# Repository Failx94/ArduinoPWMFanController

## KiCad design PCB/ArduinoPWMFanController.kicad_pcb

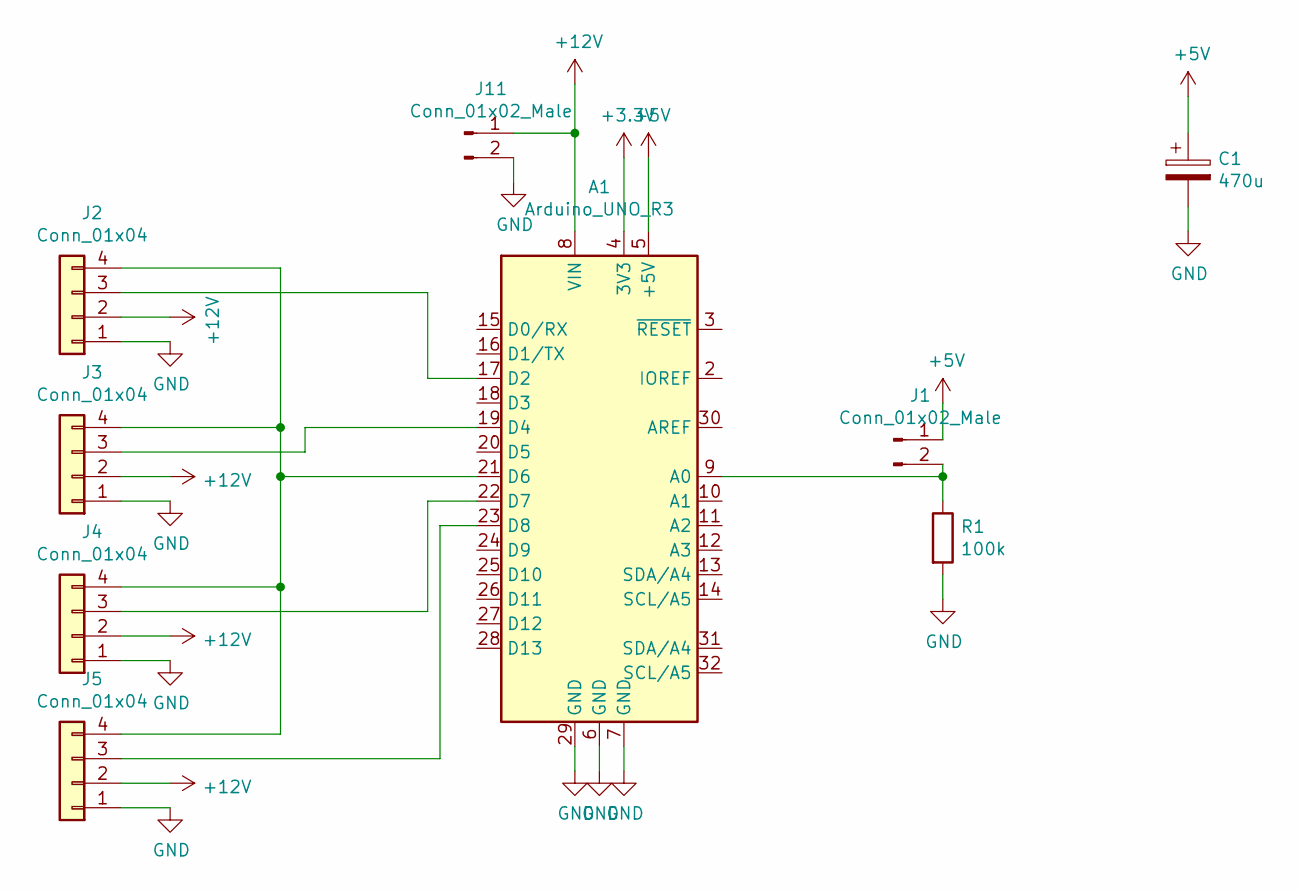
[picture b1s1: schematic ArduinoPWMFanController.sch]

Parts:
A1: Arduino_UNO_R3
C1: 470u; CP_Radial_D10.0mm_P5.00mm
J1: Conn_01x02_Male; JST_EH_B2B-EH-A_1x02_P2.50mm_Vertical
J2, J3, J4, J5: Conn_01x04; PinHeader_1x04_P2.54mm_Vertical
J11: Conn_01x02_Male; TerminalBlock_bornier-2_P5.08mm
R1: 100k; R_Axial_DIN0411_L9.9mm_D3.6mm_P12.70mm_Horizontal

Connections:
+3V3: A1.4 (3V3)
+5V: A1.5 (+5V), C1.1, J1.1
+12V: A1.8 (VIN), J2.2, J3.2, J4.2, J5.2, J11.1
GND: A1.6 (GND), A1.7 (GND), A1.29 (GND), C1.2, J2.1, J3.1, J4.1, J5.1, J11.2, R1.2
unnamed: A1.9 (A0), J1.2, R1.1
unnamed: A1.17 (D2), J2.3
unnamed: A1.19 (D4), J3.3
unnamed: A1.21 (D6), J2.4, J3.4, J4.4, J5.4
unnamed: A1.22 (D7), J4.3
unnamed: A1.23 (D8), J5.3

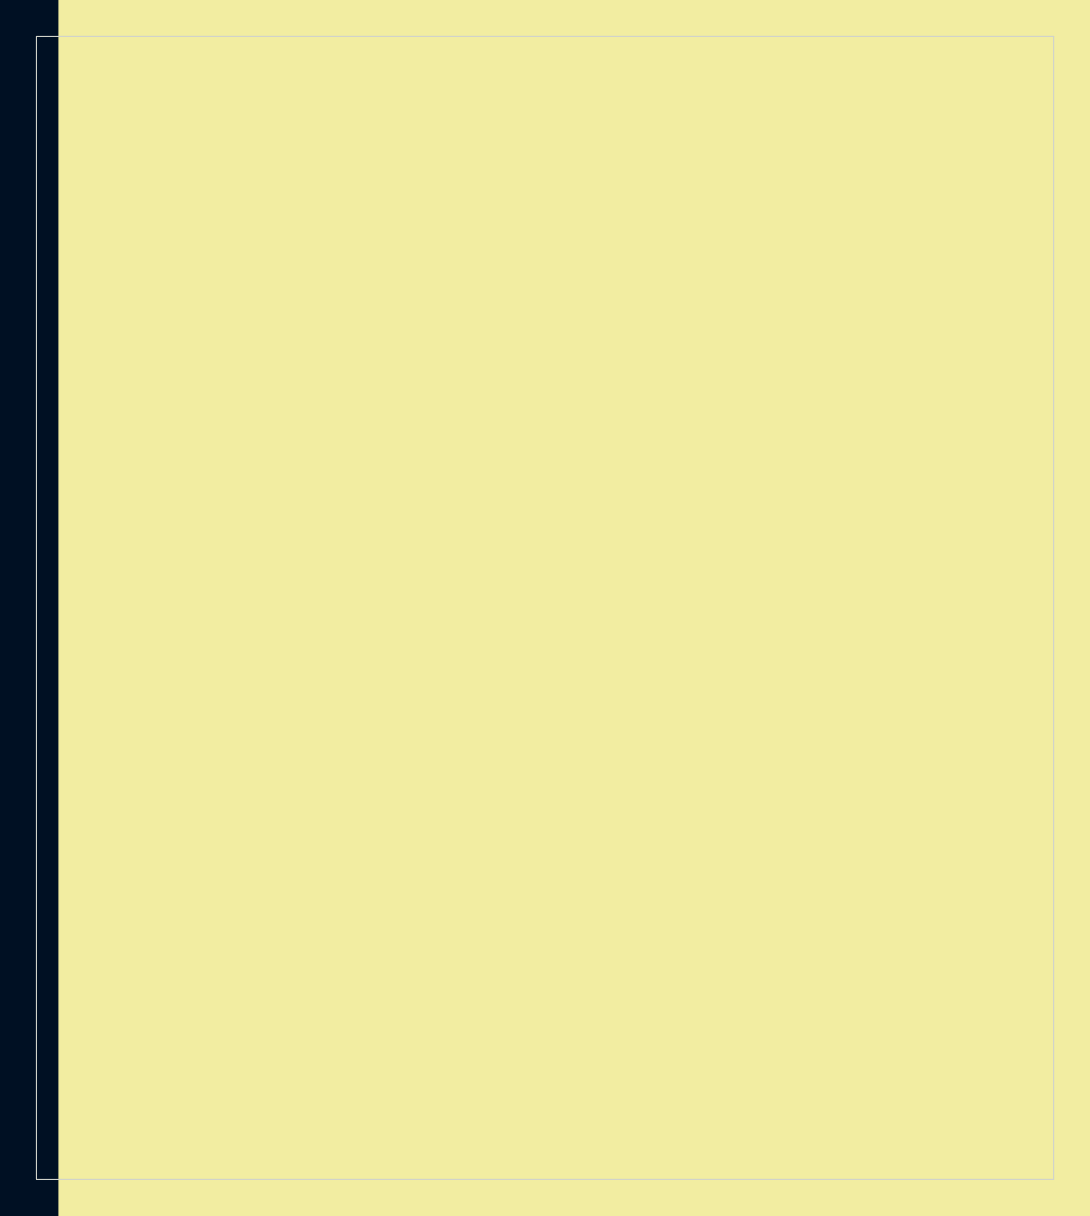
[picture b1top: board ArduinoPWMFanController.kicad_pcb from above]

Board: 2 copper layers, 56.5 x 63.5 mm, 9 parts (1 on the bottom side), 9 nets.

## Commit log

2020-05-15 Init Arduino Pro
2020-05-16 ArduinoTemp
2020-05-17 Dev Arduino Programm
